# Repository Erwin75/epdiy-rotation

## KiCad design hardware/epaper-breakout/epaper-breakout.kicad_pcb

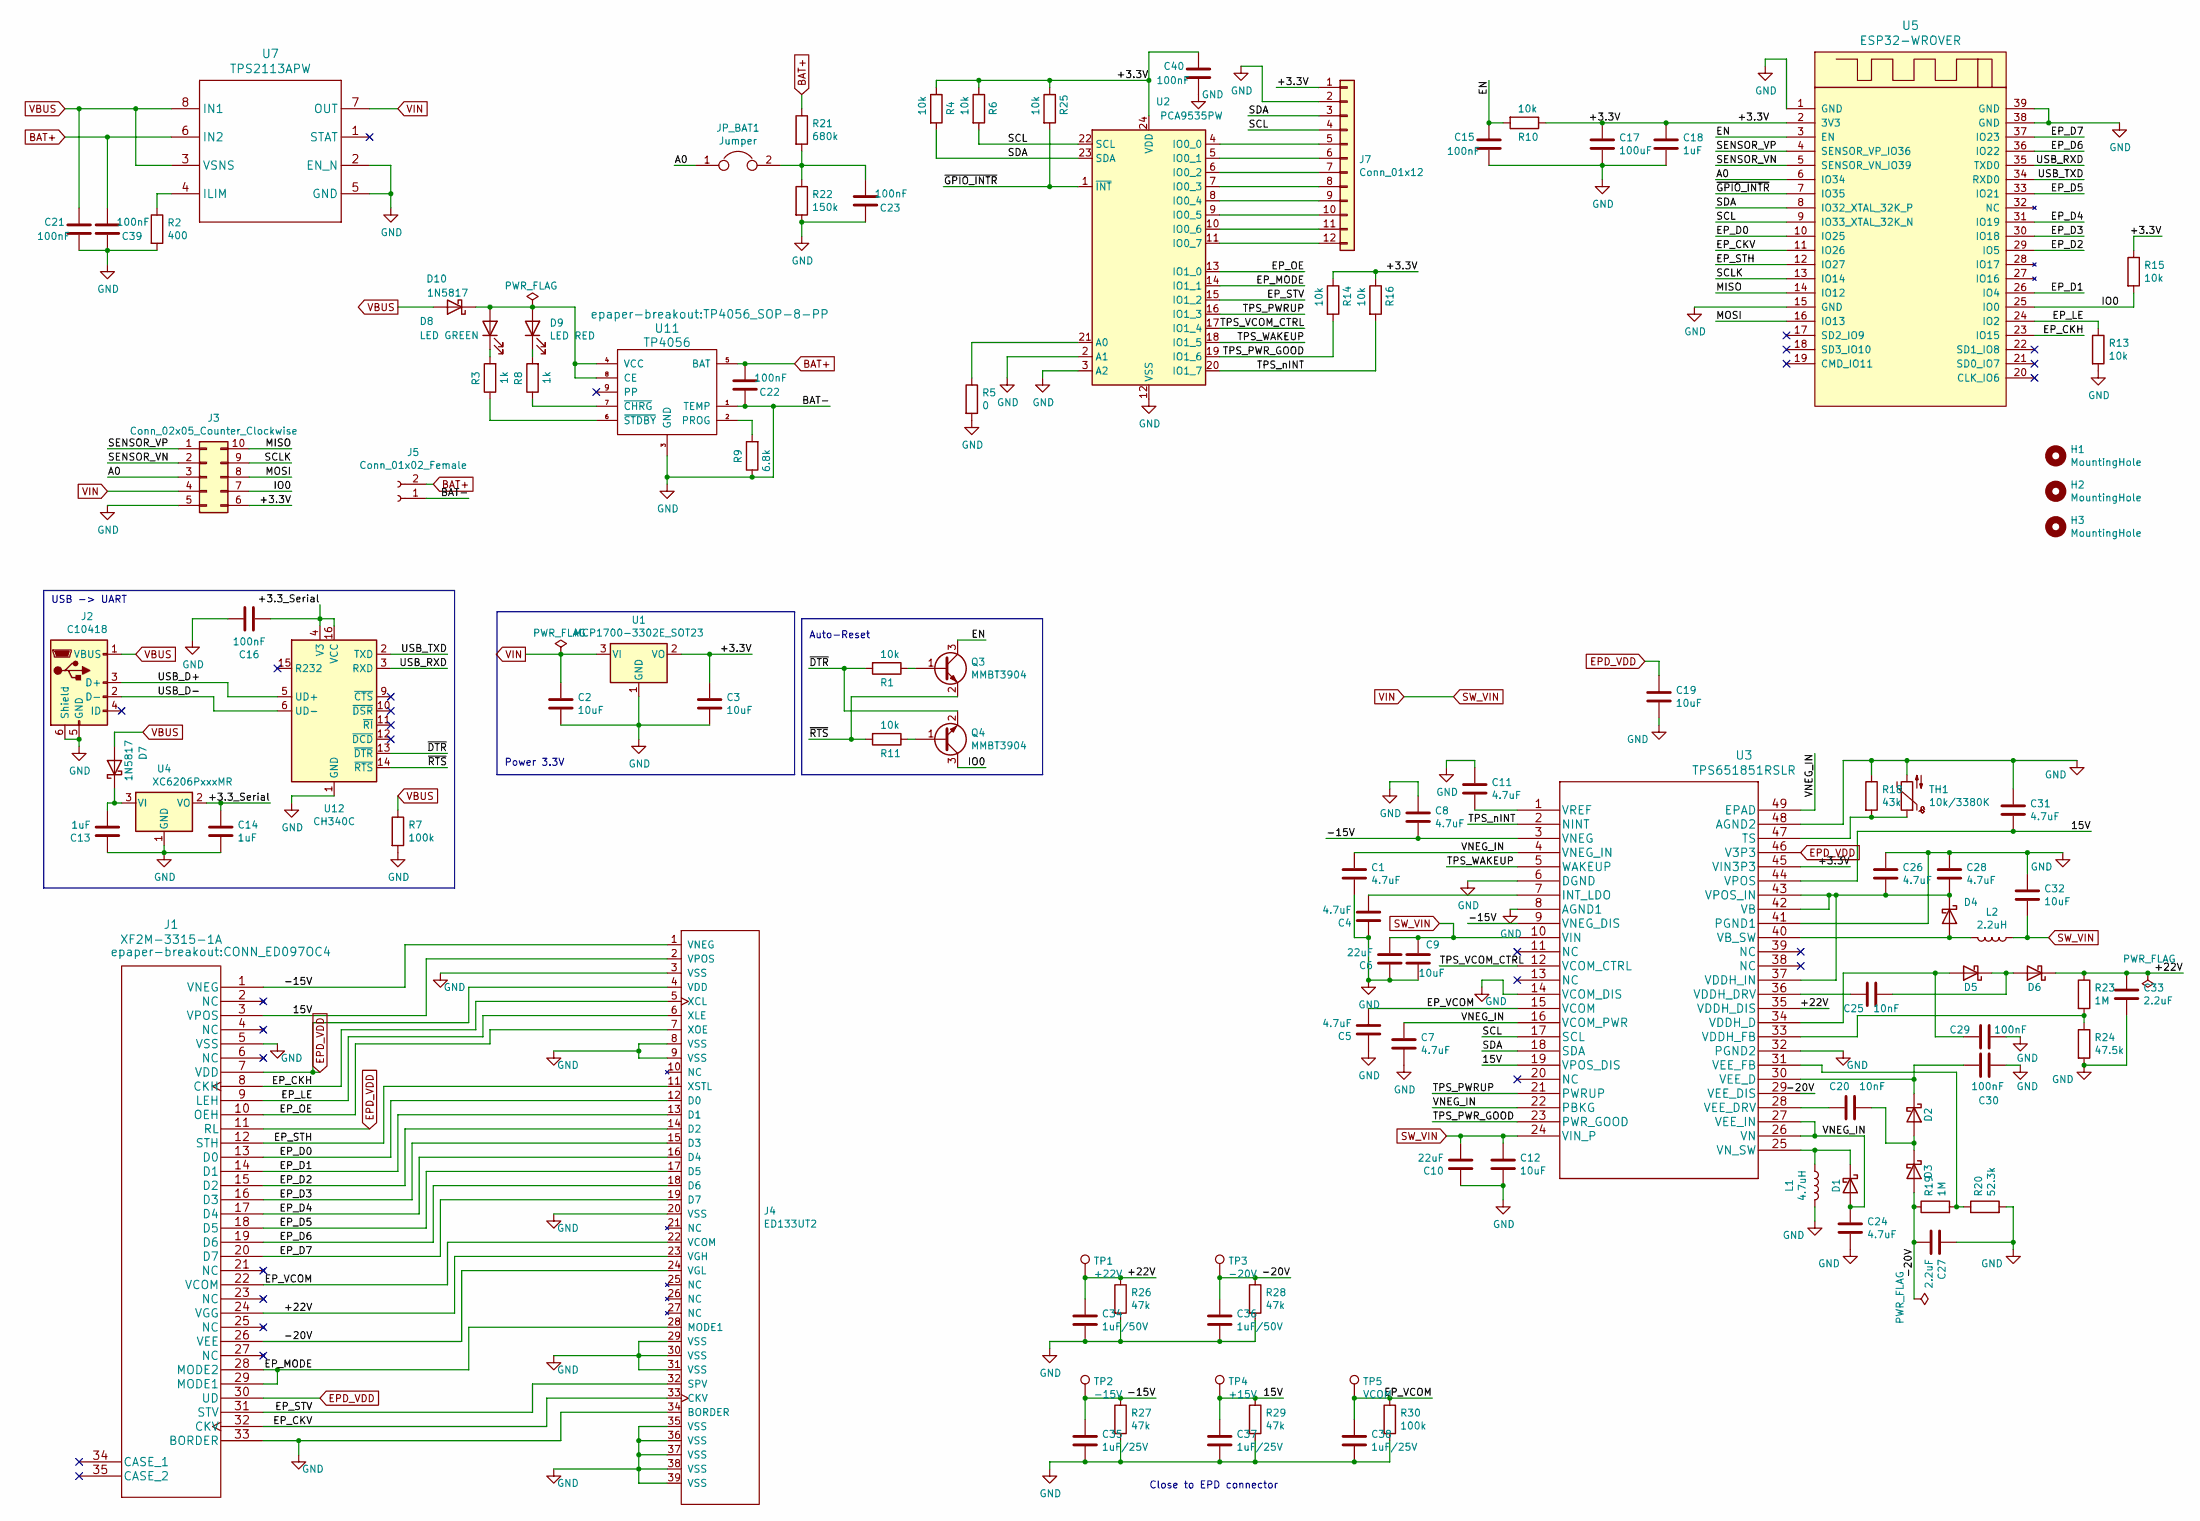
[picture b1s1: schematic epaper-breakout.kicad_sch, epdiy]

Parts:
C1, C4, C5, C7, C8, C11, C24, C26, C28, C31: 4.7uF; C_0805_2012Metric; LCSC C1779
C2, C3, C9, C12, C32: 10uF; C_0805_2012Metric; LCSC C15850
C6, C10: 22uF; C_0805_2012Metric; LCSC C45783
C13, C14, C18: 1uF; C_0805_2012Metric; LCSC C28323
C15, C16, C21, C22, C23, C29, C30, C39, C40: 100nF; C_0805_2012Metric; LCSC C49678
C17: 100uF; CP_EIA-3528-15_AVX-H; LCSC C16133
C19: 10uF; C_0805_2012Metric; LCSC C19702
C20, C25: 10nF; C_0805_2012Metric; LCSC C1710
C27, C33: 2.2uF; C_0805_2012Metric; LCSC C49217
C34, C36: 1uF/50V; C_1206_3216Metric; LCSC C1848
C35, C37, C38: 1uF/25V; C_0805_2012Metric; LCSC C28323
D1, D2, D3, D4, D5, D6: MBR0540; D_SOD-123; LCSC C21353
D7, D10: 1N5817; D_SOD-123; LCSC C8598
D8: LED GREEN; LED_0805_2012Metric; LCSC C2297
D9: LED RED; LED_0805_2012Metric; LCSC C84256
H1, H2, H3: MountingHole; MountingHole_2.2mm_M2
J1: XF2M-3315-1A; CONN_ED097OC4; LCSC C231420
J2: C10418; USB_Micro-B_A01SB141B1-067; LCSC C10418
J3: Conn_02x05_Counter_Clockwise; PinHeader_2x05_P2.54mm_Vertical
J4: ED133UT2; HRS_FH26W-39S-0.3SHW(60)
J5: Conn_01x02_Female; PinHeader_1x02_P2.54mm_Vertical
J7: Conn_01x12; PinHeader_2x06_P2.54mm_Vertical
JP_BAT1: Jumper; SolderJumper-2_P1.3mm_Bridged2Bar_RoundedPad1.0x1.5mm
L1: 4.7uH; L_Taiyo-Yuden_NR-50xx_HandSoldering; LCSC C222947
L2: 2.2uH; L_Taiyo-Yuden_NR-40xx_HandSoldering; LCSC C92959
Q3, Q4: MMBT3904; SOT-23; LCSC C20526
R1, R4, R6, R10, R11, R13, R14, R15, R16, R25: 10k; R_0603_1608Metric; LCSC C25804
R2: 400; R_0603_1608Metric; LCSC C23151
R3, R8: 1k; R_0603_1608Metric; LCSC C21190
R5: 0; R_0603_1608Metric
R7, R30: 100k; R_0603_1608Metric; LCSC C25803
R9: 6.8k; R_0603_1608Metric; LCSC C23212
R18: 43k; R_0603_1608Metric; LCSC C23172
R19, R23: 1M; R_0603_1608Metric; LCSC C22935
R20: 52.3k; R_0603_1608Metric; LCSC C23196
R21: 680k; R_0603_1608Metric; LCSC C25822
R22: 150k; R_0603_1608Metric; LCSC C22807
R24: 47.5k; R_0603_1608Metric; LCSC C25819
R26, R27, R28, R29: 47k; R_0603_1608Metric; LCSC C25819
TH1: 10k/3380K; R_0603_1608Metric; LCSC C76589
TP1: +22V; TestPoint_Pad_D2.5mm
TP2: -15V; TestPoint_Pad_D2.5mm
TP3: -20V; TestPoint_Pad_D2.5mm
TP4: +15V; TestPoint_Pad_D2.5mm
TP5: VCOM; TestPoint_Pad_D2.5mm
U1: MCP1700-3302E_SOT23; SOT-23; LCSC C39051
U2: PCA9535PW; TSSOP-24_4.4x7.8mm_P0.65mm; LCSC C255606
U3: TPS651851RSLR; LCSC C139292
U4: XC6206PxxxMR; SOT-23; LCSC C5446
U5: ESP32-WROVER; LCSC C503591
U7: TPS2113APW; LCSC C130052
U11: TP4056; TP4056_SOP-8-PP; LCSC C16581
U12: CH340C; SOIC-16_3.9x9.9mm_P1.27mm; LCSC C84681

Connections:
/15V: C31.2, C37.1, J1.3 (VPOS), J4.2 (VPOS), R29.1, TP4.1, U3.19 (VPOS_DIS), U3.44 (VPOS)
/+3.3V: C3.2, C17.1, C18.2, C40.1, J3.6, J7.1, R4.1, R6.1, R10.1, R14.1, R15.1, R16.1, R25.1, U1.2 (VO), U2.24 (VDD), U3.45 (VIN3P3), U5.2 (3V3)
/+3.3_Serial: C14.2, C16.1, U4.2 (VO), U12.4 (V3), U12.16 (VCC)
/+22V: C33.1, C34.1, D6.1 (K), J1.24 (VGG), J4.23 (VGH), R23.1, R26.1, TP1.1, U3.35 (VDDH_DIS)
/-15V: C8.2, C35.1, J1.1 (VNEG), J4.1 (VNEG), R27.1, TP2.1, U3.3 (VNEG), U3.9 (VNEG_DIS)
/-20V: C27.2, C36.1, D3.2 (A), J1.26 (VEE), J4.24 (VGL), R19.1, R28.1, TP3.1, U3.29 (VEE_DIS)
/A0: J3.3, JP_BAT1.1, U5.6 (IO34)
/EN: C15.1, Q3.3 (C), R10.2, U5.3 (EN)
/EP_CKH: J1.8 (CKH), J4.5 (XCL), U5.23 (IO15)
/EP_CKV: J1.32 (CKV), J4.33 (CKV), U5.11 (IO26)
/EP_D0: J1.13 (D0), J4.12 (D0), U5.10 (IO25)
/EP_D1: J1.14 (D1), J4.13 (D1), U5.26 (IO4)
/EP_D2: J1.15 (D2), J4.14 (D2), U5.29 (IO5)
/EP_D3: J1.16 (D3), J4.15 (D3), U5.30 (IO18)
/EP_D4: J1.17 (D4), J4.16 (D4), U5.31 (IO19)
/EP_D5: J1.18 (D5), J4.17 (D5), U5.33 (IO21)
/EP_D6: J1.19 (D6), J4.18 (D6), U5.36 (IO22)
/EP_D7: J1.20 (D7), J4.19 (D7), U5.37 (IO23)
/EP_LE: J1.9 (LEH), J4.6 (XLE), R13.1, U5.24 (IO2)
/EP_MODE: J1.28 (MODE2), J1.29 (MODE1), J4.28 (MODE1), U2.14 (IO1_1)
/EP_OE: J1.10 (OEH), J4.7 (XOE), U2.13 (IO1_0)
/EP_STH: J1.12 (STH), J4.11 (XSTL), U5.12 (IO27)
/EP_STV: J1.31 (STV), J4.32 (SPV), U2.15 (IO1_2)
/EP_VCOM: C5.2, C38.1, J1.22 (VCOM), J4.22 (VCOM), R30.1, TP5.1, U3.15 (VCOM)
/IO0: J3.7, Q4.3 (C), R15.2, U5.25 (IO0)
/MISO: J3.10, U5.14 (IO12)
/MOSI: J3.8, U5.16 (IO13)
/SCL: J7.4, R6.2, U2.22 (SCL), U3.17 (SCL), U5.9 (IO33_XTAL_32K_N)
/SCLK: J3.9, U5.13 (IO14)
/SDA: J7.3, R4.2, U2.23 (SDA), U3.18 (SDA), U5.8 (IO32_XTAL_32K_P)
/SENSOR_VN: J3.2, U5.5 (SENSOR_VN_IO39)
/SENSOR_VP: J3.1, U5.4 (SENSOR_VP_IO36)
/TPS_PWRUP: U2.16 (IO1_3), U3.21 (PWRUP)
/TPS_PWR_GOOD: R14.2, U2.19 (IO1_6), U3.23 (PWR_GOOD)
/TPS_VCOM_CTRL: U2.17 (IO1_4), U3.12 (VCOM_CTRL)
/TPS_WAKEUP: U2.18 (IO1_5), U3.5 (WAKEUP)
/TPS_nINT: R16.2, U2.20 (IO1_7), U3.2 (NINT)
/USB_D+: J2.3 (D+), U12.5 (UD+)
/USB_D-: J2.2 (D-), U12.6 (UD-)
/USB_RXD: U5.35 (TXD0), U12.3 (RXD)
/USB_TXD: U5.34 (RXD0), U12.2 (TXD)
/VNEG_IN: C1.1, C7.1, C24.1, D1.2 (A), U3.4 (VNEG_IN), U3.16 (VCOM_PWR), U3.22 (PBKG), U3.26 (VN), U3.27 (VEE_IN), U3.49 (EPAD)
/~DTR: Q4.2 (E), R1.2, U12.13 (~DTR)
/~GPIO_INTR: R25.2, U2.1 (~INT), U5.7 (IO35)
/~RTS: Q3.2 (E), R11.2, U12.14 (~RTS)
BAT+: C22.2, C39.2, J5.2, R21.1, U7.6 (IN2), U11.5 (BAT)
EPD_VDD: C19.1, J1.7 (VDD), J1.11 (RL), J1.30 (UD), J4.4 (VDD), U3.46 (V3P3)
GND: C1.2, C2.1, C3.1, C4.1, C5.1, C6.1, C7.2, C8.1, C9.2, C10.1, C11.1, C12.2, C13.2, C14.1, C15.2, C16.2, C17.2, C18.1, C19.2, C21.2, C22.1, C23.1, C24.2, C26.1, C27.1, C28.1, C29.1, C30.2, C31.1, C32.1, C33.2, C34.2, C35.2, C36.2, C37.2, C38.2, C39.1, C40.2, J1.5 (VSS), J1.33 (BORDER), J2.5 (GND), J2.6 (Shield), J3.5, J4.3 (VSS), J4.8 (VSS), J4.9 (VSS), J4.20 (VSS), J4.29 (VSS), J4.30 (VSS), J4.31 (VSS), J4.34 (BORDER), J4.35 (VSS), J4.36 (VSS), J4.37 (VSS), J4.38 (VSS), J4.39 (VSS), J5.1, J7.2, L1.2, R2.2, R5.2, R7.2, R9.1, R13.2, R18.1, R20.2, R22.2, R24.2, R26.2, R27.2, R28.2, R29.2, R30.2, TH1.2, U1.1 (GND), U2.2 (A1), U2.3 (A2), U2.12 (VSS), U3.6 (DGND), U3.8 (AGND1), U3.14 (VCOM_DIS), U3.32 (PGND2), U3.41 (PGND1), U3.48 (AGND2), U4.1 (GND), U5.1 (GND), U5.15 (GND), U5.38 (GND), U5.39 (GND), U7.2 (EN_N), U7.5 (GND), U11.1 (TEMP), U11.3 (GND), U12.1 (GND)
unnamed: C4.2, U3.7 (INT_LDO)
unnamed: C11.2, U3.1 (VREF)
unnamed: C13.1, D7.1 (K), U4.3 (VI)
unnamed: C20.1, D2.2 (A), D3.1 (K)
unnamed: C20.2, U3.28 (VEE_DRV)
unnamed: C23.2, JP_BAT1.2, R21.2, R22.1
unnamed: C25.1, D5.1 (K), D6.2 (A)
unnamed: C25.2, U3.36 (VDDH_DRV)
unnamed: C26.2, C28.2, D4.1 (K), U3.37 (VDDH_IN), U3.42 (VB), U3.43 (VPOS_IN)
unnamed: C29.2, D5.2 (A), U3.34 (VDDH_D)
unnamed: C30.1, D2.1 (K), U3.30 (VEE_D)
unnamed: D1.1 (K), L1.1, U3.25 (VN_SW)
unnamed: D4.2 (A), L2.2, U3.40 (VB_SW)
unnamed: D8.1 (K), R3.2
unnamed: D9.1 (K), R8.2
unnamed: D8.2 (A), D9.2 (A), D10.1 (K), U11.4 (VCC), U11.8 (CE)
unnamed: J7.5, U2.4 (IO0_0)
unnamed: J7.6, U2.5 (IO0_1)
unnamed: J7.7, U2.6 (IO0_2)
unnamed: J7.8, U2.7 (IO0_3)
unnamed: J7.9, U2.8 (IO0_4)
unnamed: J7.10, U2.9 (IO0_5)
unnamed: J7.11, U2.10 (IO0_6)
unnamed: J7.12, U2.11 (IO0_7)
unnamed: Q3.1 (B), R1.1
unnamed: Q4.1 (B), R11.1
unnamed: R2.1, U7.4 (ILIM)
unnamed: R3.1, U11.6 (~STDBY)
unnamed: R5.1, U2.21 (A0)
unnamed: R8.1, U11.7 (~CHRG)
unnamed: R9.2, U11.2 (PROG)
unnamed: R18.2, TH1.1, U3.47 (TS)
unnamed: R19.2, R20.1, U3.31 (VEE_FB)
unnamed: R23.2, R24.1, U3.33 (VDDH_FB)
SW_VIN: C2.2, C6.2, C9.1, C10.2, C12.1, C32.2, J3.4, L2.1, U1.3 (VI), U3.10 (VIN), U3.24 (VIN_P), U7.7 (OUT)
VBUS: C21.1, D7.2 (A), D10.2 (A), J2.1 (VBUS), R7.1, U7.3 (VSNS), U7.8 (IN1)

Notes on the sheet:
Power 3.3V
USB -> UART
Auto-Reset
Close to EPD connector

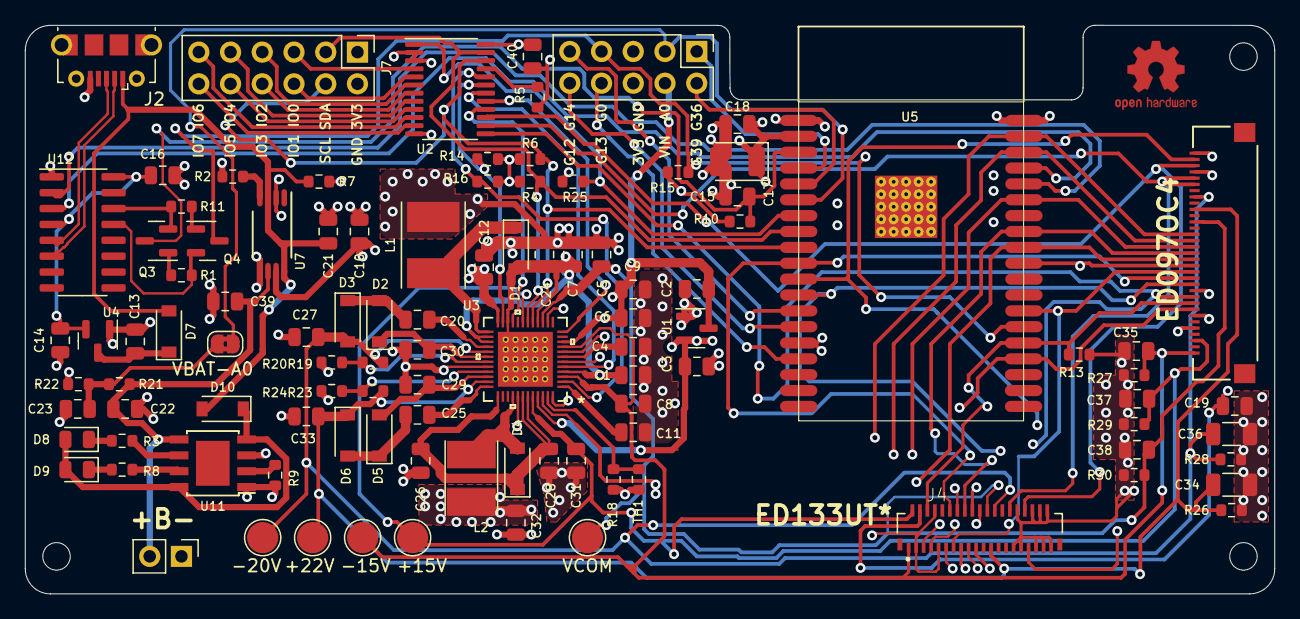
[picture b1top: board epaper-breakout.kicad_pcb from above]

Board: 4 copper layers, 100.0 x 45.5 mm, 107 parts (1 on the bottom side), 84 nets.

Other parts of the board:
CC: Symbol_CreativeCommons_SilkScreenTop_Type2_Big

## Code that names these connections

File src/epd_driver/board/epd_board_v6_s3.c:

#include "epd_board.h"
/**
 * @file epd_board_v6_s2.c
 * Do not forget that this is a different SOC, so do a:
 * idf.py fullclean             (In case you build it before on other target)
 * idf.py set-target esp32s2
 * 
 * If it get's stuck and won't change, as latest: delete the sdkconfig.default
 * Before building or it will fail
 */
#include "esp_log.h"
#include "../display_ops.h"
#include "../i2s_data_bus.h"
#include "../rmt_pulse.h"
#include "../tps65185.h"
#include <driver/gpio.h>
#include <driver/i2c.h>

static int v6_wait_for_interrupt(int timeout) __attribute__((unused));

// ESP32-S2 configuration (proposed)
#define CFG_SCL             GPIO_NUM_8
#define CFG_SDA             GPIO_NUM_9

#define EPDIY_I2C_PORT      I2C_NUM_0
#define D7 GPIO_NUM_7
#define D6 GPIO_NUM_6
#define D5 GPIO_NUM_5
#define D4 GPIO_NUM_4
#define D3 GPIO_NUM_3
#define D2 GPIO_NUM_2
#define D1 GPIO_NUM_1
#define D0 GPIO_NUM_0

/* TPS65185 5 control lines */
#define TPS_PWRGOOD       GPIO_NUM_47
#define TPS_WAKEUP        GPIO_NUM_18
#define TPS_PWRUP         GPIO_NUM_16
#define TPS_INTERRUPT     GPIO_NUM_11 // old  CFG_INTR
#define TPS_VCOM_CTRL     GPIO_NUM_10

/* EPD Control Lines */
#define CKV GPIO_NUM_35
#define STH GPIO_NUM_36
#define EPD_STV  GPIO_NUM_15
#define EPD_MODE GPIO_NUM_14
#define EPD_OE   GPIO_NUM_13
#define V4_LATCH_ENABLE GPIO_NUM_12

/* Edges */
#define CKH GPIO_NUM_21

typedef struct {
    i2c_port_t port;
    bool pwrup;
    bool vcom_ctrl;
    bool wakeup;
    bool others[8];
} epd_config_register_t;

static i2s_bus_config i2s_config = {
  .clock = CKH,
  .start_pulse = STH,
  .data_0 = D0,
  .data_1 = D1,
  .data_2 = D2,
  .data_3 = D3,
  .data_4 = D4,
  .data_5 = D5,
  .data_6 = D6,
  .data_7 = D7,
};

static bool interrupt_done = false;

static void IRAM_ATTR interrupt_handler(void* arg) {
    interrupt_done = true;
}

static int v6_wait_for_interrupt(int timeout) {
  int tries = 0;
  while (!interrupt_done && gpio_get_level(TPS_INTERRUPT) == 1) {
    if (tries >= 500) {
        return -1;
    }
    tries++;
    vTaskDelay(1);
  }
  int int1 = 0;
  int int2 = 0;
  interrupt_done = false;

  int1 = tps_read_register(EPDIY_I2C_PORT, TPS_REG_INT1);
  int2 = tps_read_register(EPDIY_I2C_PORT, TPS_REG_INT2);
  // Note: Would be nice to make an human translation of the results of this
  //       so you can get right away what's the issue without browsing datasheet
  printf("INT1: %d\n", int1);
  printf("INT2: %d\n", int2);
	int1 |= int2 << 8;

  while (!gpio_get_level(TPS_INTERRUPT)) { vTaskDelay(1); }
  return int1;
}

static epd_config_register_t config_reg;

static void epd_board_init(uint32_t epd_row_width) {
  gpio_hold_dis(CKH); // free CKH after wakeup

  i2c_config_t conf;
  conf.mode = I2C_MODE_MASTER;
  conf.sda_io_num = CFG_SDA;
  conf.scl_io_num = CFG_SCL;
  conf.sda_pullup_en = GPIO_PULLUP_ENABLE;
  conf.scl_pullup_en = GPIO_PULLUP_ENABLE;
  conf.master.clk_speed = 400000;
  conf.clk_flags = I2C_SCLK_SRC_FLAG_FOR_NOMAL;
  ESP_ERROR_CHECK(i2c_param_config(EPDIY_I2C_PORT, &conf));

  ESP_ERROR_CHECK(i2c_driver_install(EPDIY_I2C_PORT, I2C_MODE_MASTER, 0, 0, 0));

  config_reg.port = EPDIY_I2C_PORT;
  config_reg.pwrup = false;
  config_reg.vcom_ctrl = false;
  config_reg.wakeup = false;
  for (int i=0; i<8; i++) {
      config_reg.others[i] = false;
  }

    /*  
     TPS_VCOM_CTRL     Output 
     TPS_WAKEUP        Output
     TPS_PWRUP         Output
     TPS_INTERRUPT     Input now CFG_INTR
     TPS_PWRGOOD       Input
     */
    // Control lines are now controlled directly  (1->4) by S2
    // Also TPS65185 control pins are set up here (4->8)
    gpio_num_t EP_CONTROL[] = {STH, EPD_STV, EPD_MODE, EPD_OE, V4_LATCH_ENABLE, TPS_WAKEUP, TPS_PWRUP, TPS_VCOM_CTRL};
   
    for (int x = 0; x < 8; x++) {
        printf("IO %d to LOW (loop:%d)\n", (int)EP_CONTROL[x], x);
        // Added because certain Pins like IO42 would not turn HI withouth resetting them first
        gpio_reset_pin(EP_CONTROL[x]);
        gpio_set_direction(EP_CONTROL[x], GPIO_MODE_OUTPUT);
        gpio_set_level(EP_CONTROL[x], 0);
    }
    gpio_set_direction(TPS_PWRGOOD, GPIO_MODE_INPUT);
    // TODO: Interrupts should be added for incoming signals from TPS65185
    gpio_set_direction(TPS_INTERRUPT, GPIO_MODE_INPUT);
    gpio_set_intr_type(TPS_INTERRUPT, GPIO_INTR_NEGEDGE);
    ESP_ERROR_CHECK(gpio_install_isr_service(0));
    ESP_ERROR_CHECK(gpio_isr_handler_add(TPS_INTERRUPT, interrupt_handler, (void *) TPS_INTERRUPT));

  // Setup I2S
  // add an offset off dummy bytes to allow for enough timing headroom
  i2s_bus_init( &i2s_config , epd_row_width + 32);

  rmt_pulse_init(CKV);
}

static void epd_board_deinit() {
  //gpio_reset_pin(TPS_INTERRUPT);
  //rtc_gpio_isolate(TPS_INTERRUPT);
  gpio_set_level(TPS_VCOM_CTRL, 0);
  gpio_set_level(TPS_PWRUP, 0);

  int tries = 0;
  while (gpio_get_level(TPS_PWRGOOD) == 1) {
    if (tries >= 500) {
      ESP_LOGE("epdiy", "failed to shut down TPS65185!");
      break;
    }
    tries++;
    vTaskDelay(1);
  }
  // Not sure why we need this delay, but the TPS65185 seems to generate an interrupt after some time that needs to be cleared.
  vTaskDelay(500);
  ESP_LOGI("epdiy", "going to sleep.");
  i2c_driver_delete(EPDIY_I2C_PORT);
}

static void epd_board_set_ctrl(epd_ctrl_state_t *state, const epd_ctrl_state_t * const mask) {
  uint8_t value = 0x00;
  if (state->ep_sth) {
    fast_gpio_set_hi(STH);
  } else {
    fast_gpio_set_lo(STH);
  }

  if (mask->ep_output_enable || mask->ep_mode || mask->ep_stv) {
    if (state->ep_output_enable) gpio_set_level(EPD_OE, 1);
    if (state->ep_mode)          gpio_set_level(EPD_MODE, 1);
    if (state->ep_stv)           gpio_set_level(EPD_STV, 1);
    if (config_reg.pwrup)        gpio_set_level(TPS_PWRUP, 1);
    if (config_reg.vcom_ctrl)    gpio_set_level(TPS_VCOM_CTRL, 1);
    if (config_reg.wakeup)       gpio_set_level(TPS_WAKEUP, 1);
  }

  if (state->ep_latch_enable) {
    fast_gpio_set_hi(V4_LATCH_ENABLE);
  } else {
    fast_gpio_set_lo(V4_LATCH_ENABLE);
  }
}

static void epd_board_poweron(epd_ctrl_state_t *state) {
  i2s_gpio_attach(&i2s_config);

  epd_ctrl_state_t mask = {
    .ep_stv = true,
  };
  state->ep_stv = true;
  config_reg.wakeup = true;
  epd_board_set_ctrl(state, &mask);
  config_reg.pwrup = true;
  epd_board_set_ctrl(state, &mask);
  config_reg.vcom_ctrl = true;
  epd_board_set_ctrl(state, &mask);

  // give the IC time to powerup and set lines
  vTaskDelay(1);

  printf("\nThermistor °C: %d\n", tps_read_thermistor(EPDIY_I2C_PORT));
  printf("Waiting for PWRGOOD...\n");
  // while (!(pca9555_read_input(reg->port, 1) & CFG_PIN_PWRGOOD)) {
  while (gpio_get_level(TPS_PWRGOOD) == 0) {
      vTaskDelay(5);
  }
  printf("TPS_PWRGOOD ok\n");

  ESP_ERROR_CHECK(tps_write_register(config_reg.port, TPS_REG_ENABLE, 0x3F));

#ifdef CONFIG_EPD_DRIVER_S2_VCOM
  tps_set_vcom(config_reg.port, CONFIG_EPD_DRIVER_S2_VCOM);
// Arduino IDE...
#else
  extern int epd_driver_v6_vcom;
  tps_set_vcom(config_reg.port, epd_driver_v6_vcom);
#endif

  state->ep_sth = true;
  mask = (const epd_ctrl_state_t){
    .ep_sth = true,
  };
  epd_board_set_ctrl(state, &mask);

  int tries = 0;
  while (!((tps_read_register(config_reg.port, TPS_REG_PG) & 0xFA) == 0xFA)) {
    if (tries >= 500) {
      ESP_LOGE("epdiy", "Power enable failed! PG status: %X", tps_read_register(config_reg.port, TPS_REG_PG));
      return;
    }
    tries++;
    vTaskDelay(1);
  }
}

static void epd_board_poweroff(epd_ctrl_state_t *state) {
  epd_ctrl_state_t mask = {
    .ep_stv = true,
    .ep_output_enable = true,
    .ep_mode = true,
  };
  config_reg.vcom_ctrl = false;
  config_reg.pwrup = false;
  state->ep_stv = false;
  state->ep_output_enable = false;
  state->ep_mode = false;
  epd_board_set_ctrl(state, &mask);
  vTaskDelay(1);
  config_reg.wakeup = false;
  epd_board_set_ctrl(state, &mask);

  i2s_gpio_detach(&i2s_config);
}

static float epd_board_ambient_temperature() {
  return tps_read_thermistor(EPDIY_I2C_PORT);
}

// Nicely made
const EpdBoardDefinition epd_board_s3 = {
  .init = epd_board_init,
  .deinit = epd_board_deinit,
  .set_ctrl = epd_board_set_ctrl,
  .poweron = epd_board_poweron,
  .poweroff = epd_board_poweroff,

  .temperature_init = NULL,
  .ambient_temperature = epd_board_ambient_temperature,
};

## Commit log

2022-01-24 Measure epd_hl_update_screen time
2022-02-10 Add I2S lines down for Lilyo board https://github.com/vroland/epdiy/issues/136
2022-02-20 Modified version adding 13.3 connector #4
2022-02-20 #4 Fix some DRC warnings
2022-03-27 Add untested S2 board to https://github.com/vroland/epdiy/pull/168
2022-04-10 Add support also for S3 board. Extend PSRAM example to support S2
2022-04-14 Update TPS_PWRGOOD to IO47
2022-05-18 Testing exclusively S2 with right voltages REF https://github.com/vroland/epdiy/issues/144
2022-06-01 Assign CLK for I2S in S2 using IO MUX
2022-06-01 Now I2S clock is running as expected!
2022-06-06 S2 further signals correction
2023-01-03 removed boards
2023-01-04 removed i2s_data_bus.c

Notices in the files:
hardware/epaper-breakout/epaper-breakout.kicad_sch:
License: CC-BY-SA-4.0
parts and their libraries:
Copyright 2016 Accelerated Designs. All rights reserved.
